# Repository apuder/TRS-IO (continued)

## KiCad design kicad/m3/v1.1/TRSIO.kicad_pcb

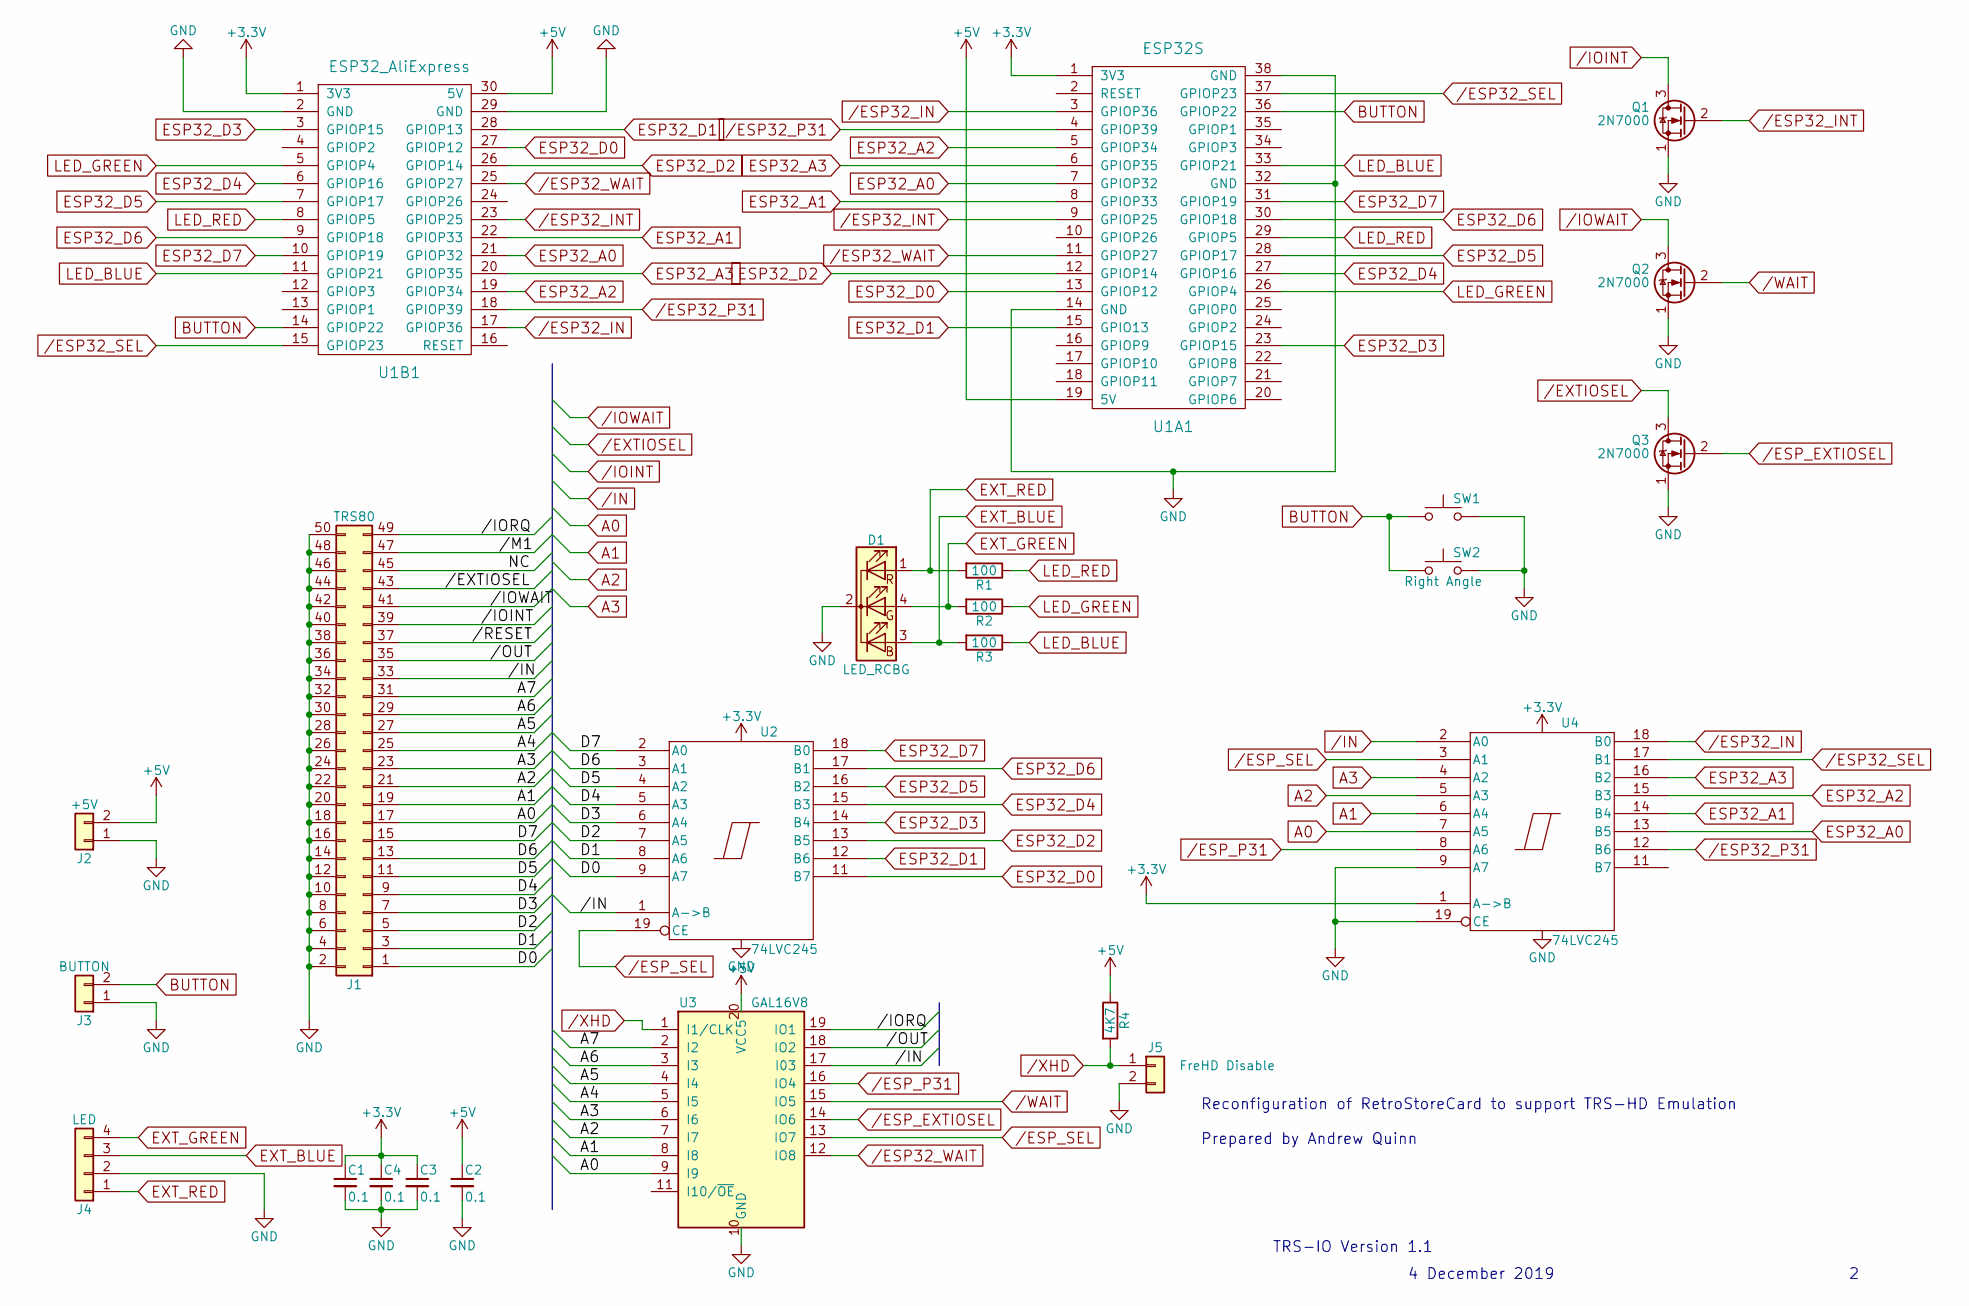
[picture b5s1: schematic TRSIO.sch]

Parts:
C1, C2, C3, C4: 0.1; C_Disc_D3.0mm_W2.0mm_P2.50mm
D1: LED_RCBG; LED_D5.0mm-4
J1: TRS80; Pin_Header_Straight_2x25_Pitch2.54mm
J2: +5V; Pin_Header_Straight_1x02_Pitch2.54mm
J3: BUTTON; Pin_Header_Straight_1x02_Pitch2.54mm
J4: LED; Pin_Header_Straight_1x04_Pitch2.54mm
J5: FreHD Disable; Pin_Header_Straight_1x02_Pitch2.54mm
Q1, Q2, Q3: 2N7000; TO-92_Molded_Narrow
R1, R2, R3: 100; R_Axial_DIN0207_L6.3mm_D2.5mm_P7.62mm_Horizontal
R4: 4K7; R_Axial_DIN0207_L6.3mm_D2.5mm_P7.62mm_Horizontal
SW1: SW_Push; SW_PUSH_6mm_h9.5mm
SW2: Right Angle; SW_Tactile_SPST_Angled_PTS645Vx31-2LFS
U1A1: ESP32S; DIP-38_W22.9mm
U1B1: ESP32_AliExpress; DIP-30_W25.4mm
U2, U4: 74LVC245; DIP-20_W7.62mm
U3: GAL16V8; DIP-20_W7.62mm

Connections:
+3V3: C1.1, C3.1, C4.1, U1A1.1 (3V3), U1B1.1 (3V3), U2.20 (VCC), U4.1 (A->B), U4.20 (VCC)
+5V: C2.1, J2.2, R4.1, U1A1.19 (5V), U1B1.30 (5V), U3.20 (VCC5)
//IORQ: J1.49, U3.19 (IO1)
//M1: J1.47
//OUT: J1.35, U3.18 (IO2)
//RESET: J1.37
/A4: J1.25, U3.5 (I5)
/A5: J1.27, U3.4 (I4)
/A6: J1.29, U3.3 (I3)
/A7: J1.31, U3.2 (I2)
/D0: J1.1, U2.9 (A7)
/D1: J1.3, U2.8 (A6)
/D2: J1.5, U2.7 (A5)
/D3: J1.7, U2.6 (A4)
/D4: J1.9, U2.5 (A3)
/D5: J1.11, U2.4 (A2)
/D6: J1.13, U2.3 (A1)
/D7: J1.15, U2.2 (A0)
/ESP32_IN: U1A1.3 (GPIOP36), U1B1.17 (GPIOP36), U4.18 (B0)
/ESP32_INT: Q1.2 (G), U1A1.9 (GPIOP25), U1B1.23 (GPIOP25)
/ESP32_P31: U1A1.4 (GPIOP39), U1B1.18 (GPIOP39), U4.12 (B6)
/ESP32_SEL: U1A1.37 (GPIOP23), U1B1.15 (GPIOP23), U4.17 (B1)
/ESP32_WAIT: U1A1.11 (GPIOP27), U1B1.25 (GPIOP27), U3.12 (IO8)
/ESP_EXTIOSEL: Q3.2 (G), U3.14 (IO6)
/ESP_P31: U3.16 (IO4), U4.8 (A6)
/ESP_SEL: U2.19 (CE), U3.13 (IO7), U4.3 (A1)
/EXTIOSEL: J1.43, Q3.3 (D)
/IN: J1.33, U2.1 (A->B), U3.17 (I03), U4.2 (A0)
/IOINT: J1.39, Q1.3 (D)
/IOWAIT: J1.41, Q2.3 (D)
/NC: J1.45
/WAIT: Q2.2 (G), U3.15 (IO5)
/XHD: J5.1, R4.2, U3.1 (I1/CLK)
A0: J1.17, U3.9 (I9), U4.7 (A5)
A1: J1.19, U3.8 (I8), U4.6 (A4)
A2: J1.21, U3.7 (I7), U4.5 (A3)
A3: J1.23, U3.6 (I6), U4.4 (A2)
BUTTON: J3.2, SW1.1, SW2.1, U1A1.36 (GPIOP22), U1B1.14 (GPIOP22)
ESP32_A0: U1A1.7 (GPIOP32), U1B1.21 (GPIOP32), U4.13 (B5)
ESP32_A1: U1A1.8 (GPIOP33), U1B1.22 (GPIOP33), U4.14 (B4)
ESP32_A2: U1A1.5 (GPIOP34), U1B1.19 (GPIOP34), U4.15 (B3)
ESP32_A3: U1A1.6 (GPIOP35), U1B1.20 (GPIOP35), U4.16 (B2)
ESP32_D0: U1A1.13 (GPIOP12), U1B1.27 (GPIOP12), U2.11 (B7)
ESP32_D1: U1A1.15 (GPIO13), U1B1.28 (GPIOP13), U2.12 (B6)
ESP32_D2: U1A1.12 (GPIOP14), U1B1.26 (GPIOP14), U2.13 (B5)
ESP32_D3: U1A1.23 (GPIOP15), U1B1.3 (GPIOP15), U2.14 (B4)
ESP32_D4: U1A1.27 (GPIOP16), U1B1.6 (GPIOP16), U2.15 (B3)
ESP32_D5: U1A1.28 (GPIOP17), U1B1.7 (GPIOP17), U2.16 (B2)
ESP32_D6: U1A1.30 (GPIOP18), U1B1.9 (GPIOP18), U2.17 (B1)
ESP32_D7: U1A1.31 (GPIOP19), U1B1.10 (GPIOP19), U2.18 (B0)
EXT_BLUE: D1.3 (BA), J4.3, R3.2
EXT_GREEN: D1.4 (GA), J4.4, R2.2
EXT_RED: D1.1 (RA), J4.1, R1.2
GND: C1.2, C2.2, C3.2, C4.2, D1.2 (K), J1.2, J1.4, J1.6, J1.8, J1.10, J1.12, J1.14, J1.16, J1.18, J1.20, J1.22, J1.24, J1.26, J1.28, J1.30, J1.32, J1.34, J1.36, J1.38, J1.40, J1.42, J1.44, J1.46, J1.48, J1.50, J2.1, J3.1, J4.2, J5.2, Q1.1 (S), Q2.1 (S), Q3.1 (S), SW1.2, SW2.2, U1A1.14 (GND), U1A1.32 (GND), U1A1.38 (GND), U1B1.2 (GND), U1B1.29 (GND), U2.10 (GND), U3.10 (GND), U4.9 (A7), U4.10 (GND), U4.19 (CE)
LED_BLUE: R3.1, U1A1.33 (GPIOP21), U1B1.11 (GPIOP21)
LED_GREEN: R2.1, U1A1.26 (GPIOP4), U1B1.5 (GPIOP4)
LED_RED: R1.1, U1A1.29 (GPIOP5), U1B1.8 (GPIOP5)

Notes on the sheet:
Reconfiguration of RetroStoreCard to support TRS-HD Emulation Prepared by Andrew Quinn
4 December 2019
TRS-IO Version 1.1

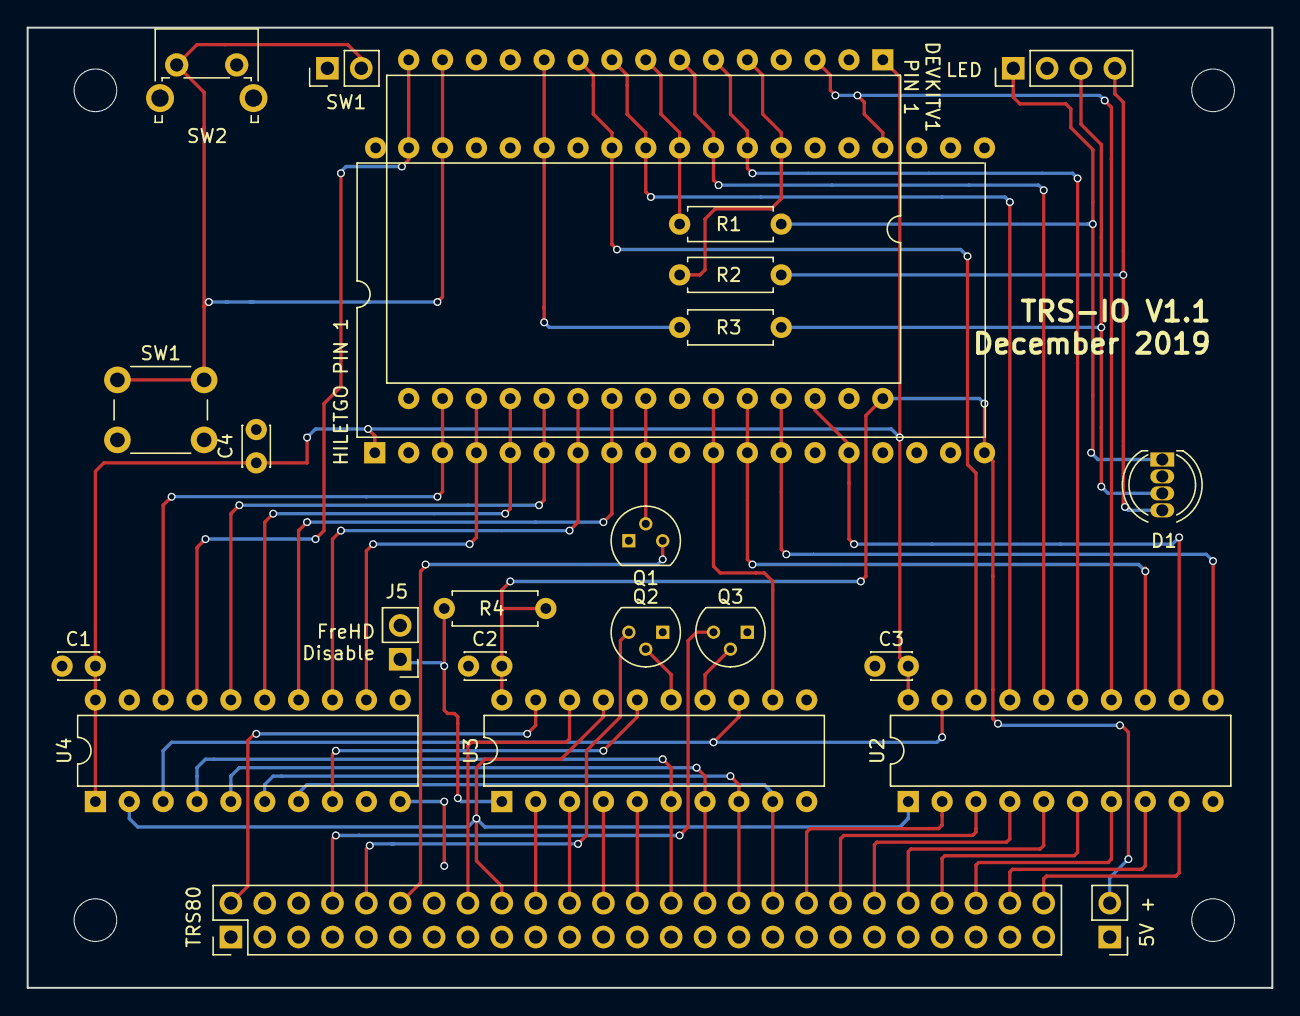
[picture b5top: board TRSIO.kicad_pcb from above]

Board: 2 copper layers, 93.3 x 72.0 mm, 24 parts (0 on the bottom side), 54 nets.
